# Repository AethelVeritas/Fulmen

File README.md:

# Fulmen
A small wireless low-profile split keyboard.

Shield: [![CC BY-NC-SA 4.0][cc-by-nc-sa-shield]][cc-by-nc-sa]

This work is licensed under a
[Creative Commons Attribution-NonCommercial-ShareAlike 4.0 International License][cc-by-nc-sa].

[![CC BY-NC-SA 4.0][cc-by-nc-sa-image]][cc-by-nc-sa]

[cc-by-nc-sa]: http://creativecommons.org/licenses/by-nc-sa/4.0/
[cc-by-nc-sa-image]: https://licensebuttons.net/l/by-nc-sa/4.0/88x31.png
[cc-by-nc-sa-shield]: https://img.shields.io/badge/License-CC%20BY--NC--SA%204.0-lightgrey.svg

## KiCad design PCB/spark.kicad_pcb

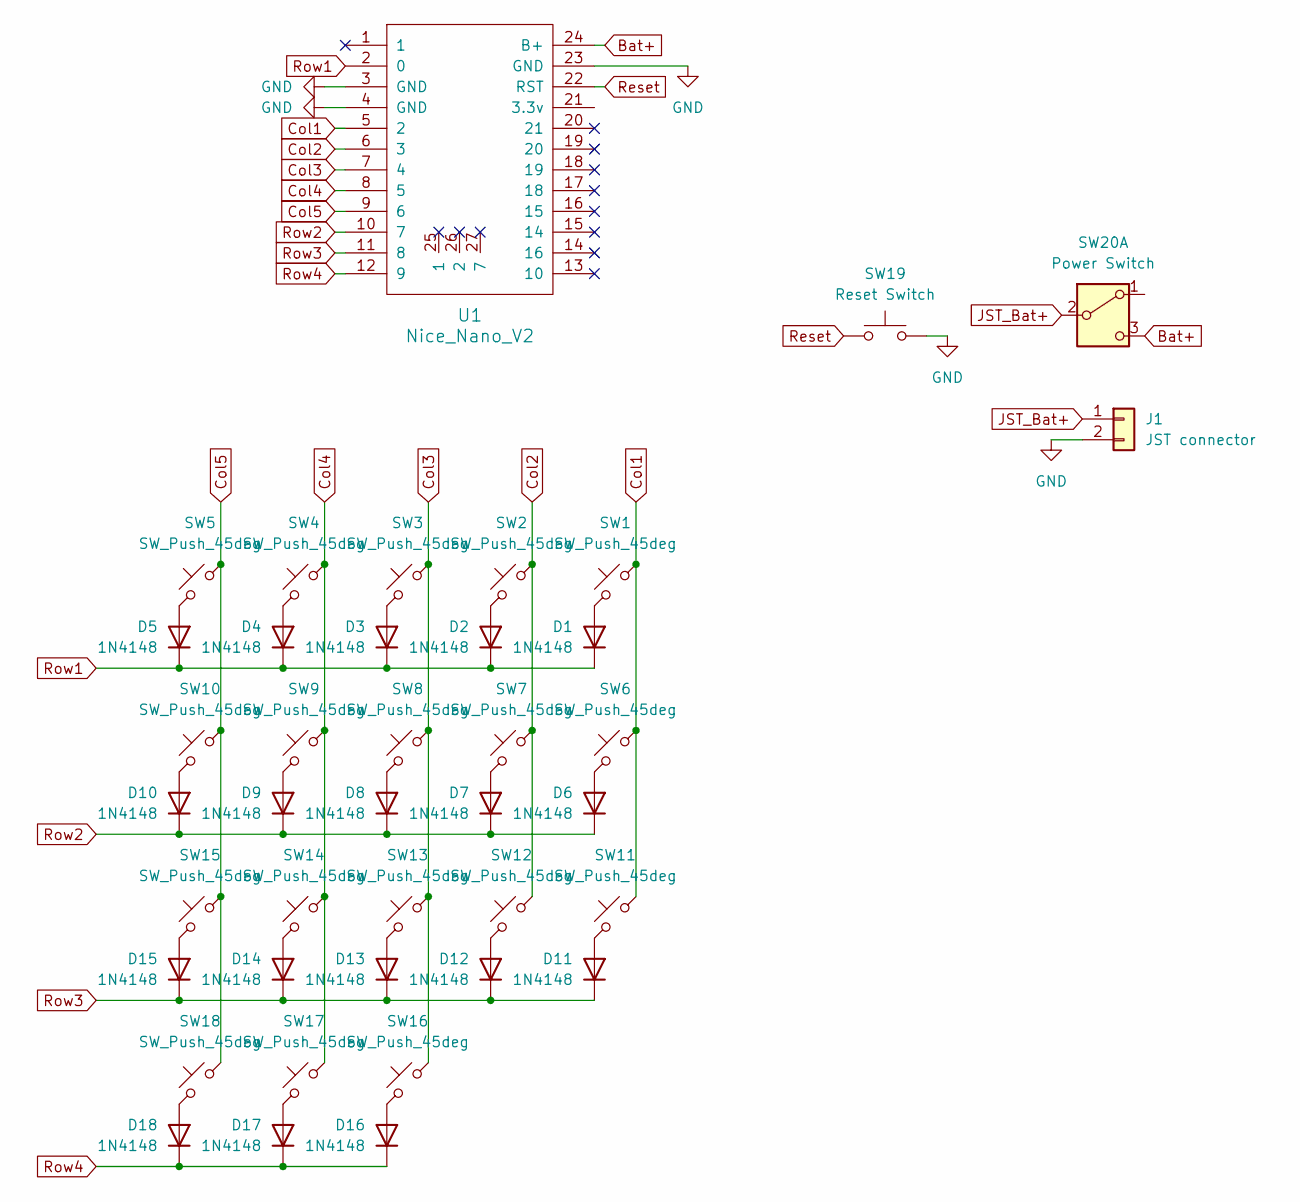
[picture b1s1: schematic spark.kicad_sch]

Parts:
D1, D2, D3, D4, D5, D6, D7, D8, D9, D10, D11, D12, D13, D14, D15, D16, D17, D18: 1N4148; 1N4148 Cutout Diode
J1: JST connector; Connector_1x02_JST-PH
SW1, SW2, SW3, SW4, SW5, SW6, SW7, SW8, SW9, SW10, SW11, SW12, SW13, SW14, SW15, SW16, SW17, SW18: SW_Push_45deg
SW19: Reset Switch; SW_SPST_B3U-1000P_Reversible
SW20: Power Switch; SW_MSK12C02-HB_Reversible
U1: Nice_Nano_V2

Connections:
Bat+: SW20.3 (C), U1.24 (B+)
Col1: SW1.1, SW6.1, SW11.1, U1.5 (2)
Col2: SW2.1, SW7.1, SW12.1, U1.6 (3)
Col3: SW3.1, SW8.1, SW13.1, SW16.1, U1.7 (4)
Col4: SW4.1, SW9.1, SW14.1, SW17.1, U1.8 (5)
Col5: SW5.1, SW10.1, SW15.1, SW18.1, U1.9 (6)
GND: J1.2, SW19.2, U1.3 (GND), U1.4 (GND), U1.23 (GND)
JST_Bat+: J1.1, SW20.2 (B)
unnamed: D1.2 (A), SW1.2
unnamed: D2.2 (A), SW2.2
unnamed: D3.2 (A), SW3.2
unnamed: D4.2 (A), SW4.2
unnamed: D5.2 (A), SW5.2
unnamed: D6.2 (A), SW6.2
unnamed: D7.2 (A), SW7.2
unnamed: D8.2 (A), SW8.2
unnamed: D9.2 (A), SW9.2
unnamed: D10.2 (A), SW10.2
unnamed: D11.2 (A), SW11.2
unnamed: D12.2 (A), SW12.2
unnamed: D13.2 (A), SW13.2
unnamed: D14.2 (A), SW14.2
unnamed: D15.2 (A), SW15.2
unnamed: D16.2 (A), SW16.2
unnamed: D17.2 (A), SW17.2
unnamed: D18.2 (A), SW18.2
Reset: SW19.1, U1.22 (RST)
Row1: D1.1 (K), D2.1 (K), D3.1 (K), D4.1 (K), D5.1 (K), U1.2 (0)
Row2: D6.1 (K), D7.1 (K), D8.1 (K), D9.1 (K), D10.1 (K), U1.10 (7)
Row3: D11.1 (K), D12.1 (K), D13.1 (K), D14.1 (K), D15.1 (K), U1.11 (8)
Row4: D16.1 (K), D17.1 (K), D18.1 (K), U1.12 (9)

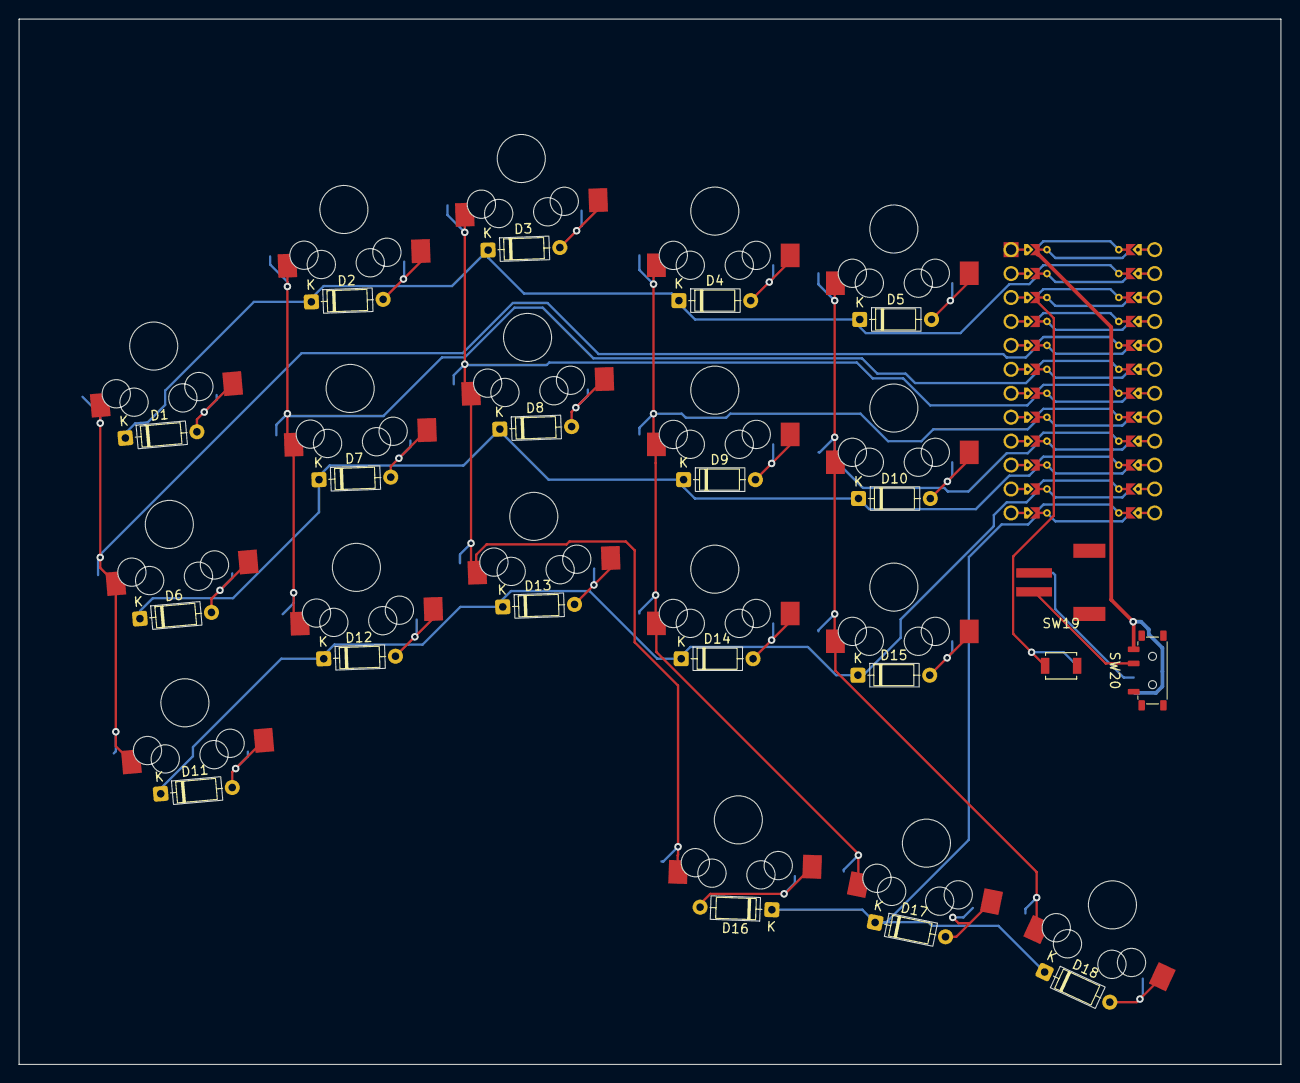
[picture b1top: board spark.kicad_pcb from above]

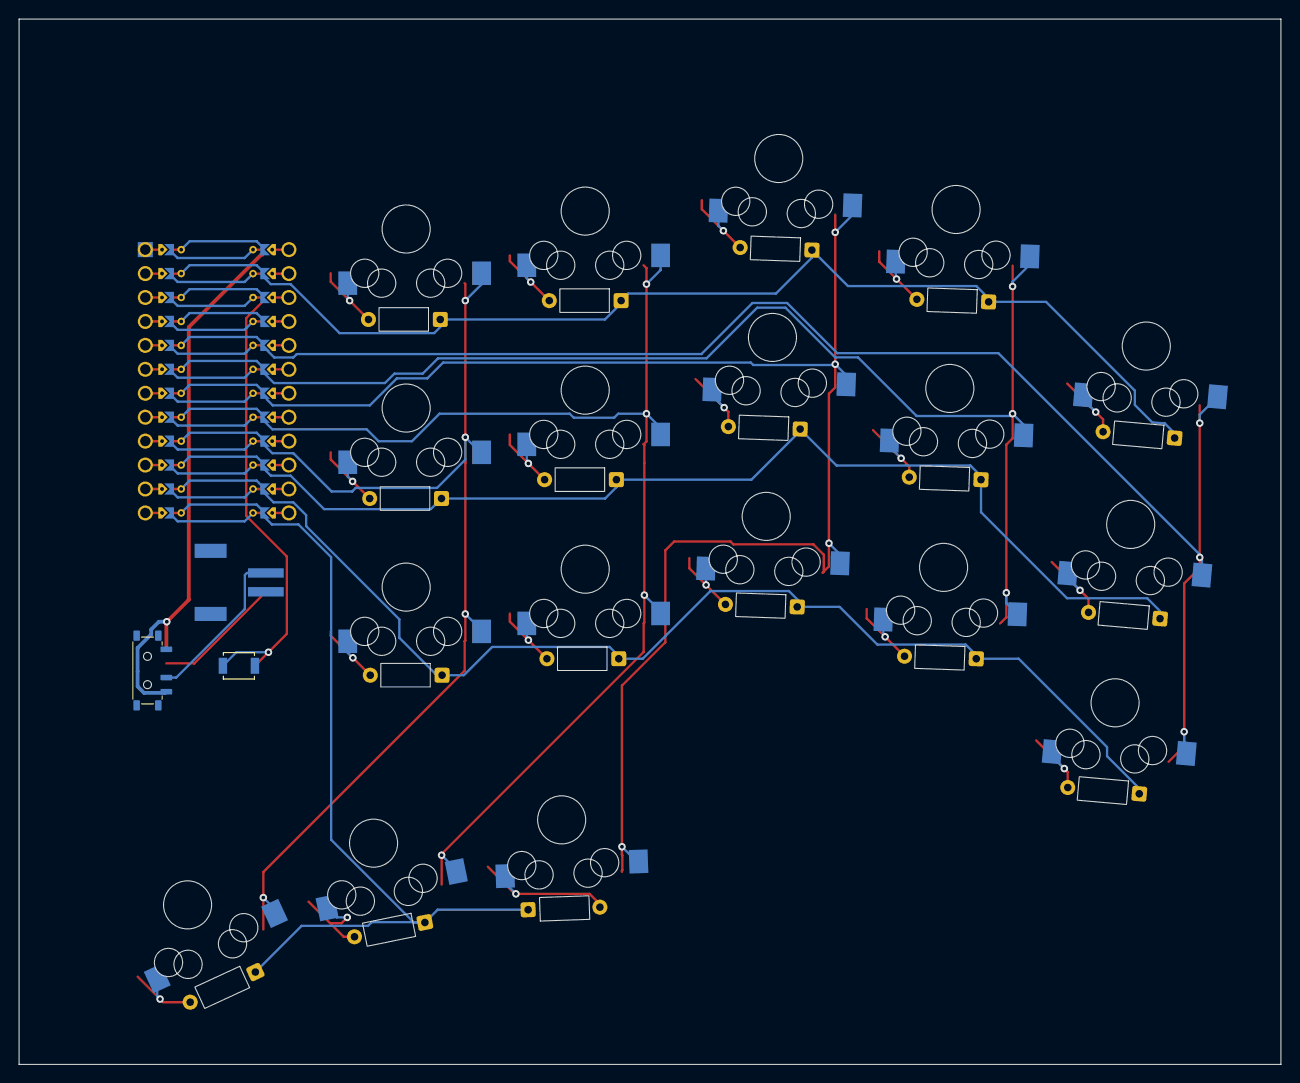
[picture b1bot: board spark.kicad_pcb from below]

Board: 2 copper layers, 133.9 x 110.9 mm, 40 parts (18 on the bottom side), 31 nets.

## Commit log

2025-08-12 Added entry for JOURNAL.md
2025-08-12 test README
2025-08-19 Updated JOURNAL.md and added PCB files
2025-08-19 Added pics
2025-08-19 Fixed image path error in JOURNAL.md
2025-08-22 Routed everything
2025-08-24 Edited JOURNAL.md
2025-08-24 Finished PCB, renamed to Fulmen
2025-08-24 Update README.md
    changed to fulmen
2025-08-25 Final version, silkscreen still giving errors though.
2025-08-25 deletions and renaming of fulmen to Fulmen
2025-08-25 updated journal
2025-08-30 Updated PCB because some traces were cut by diode cutouts
